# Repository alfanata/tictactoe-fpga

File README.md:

# Tic Tac Toe game for ice40 FPGA (HX8K)

* Simple tic-tac-toe game for the HX8K FPGA breakout board.

* Can both be played against AI or with 2 human players by setting a switch.

* The AI is based on generating the gametree using the python script and then storing all moves in the BRAM of the FPGA as a ROM. The python script generates the entire BRAM block initialization code.

* A PCB design is also provided that can plug directly into the HX8K breakout board. 

* To support other FPGA's you will have to modify the tictactoe_ram entity to fit other native BRAM types.

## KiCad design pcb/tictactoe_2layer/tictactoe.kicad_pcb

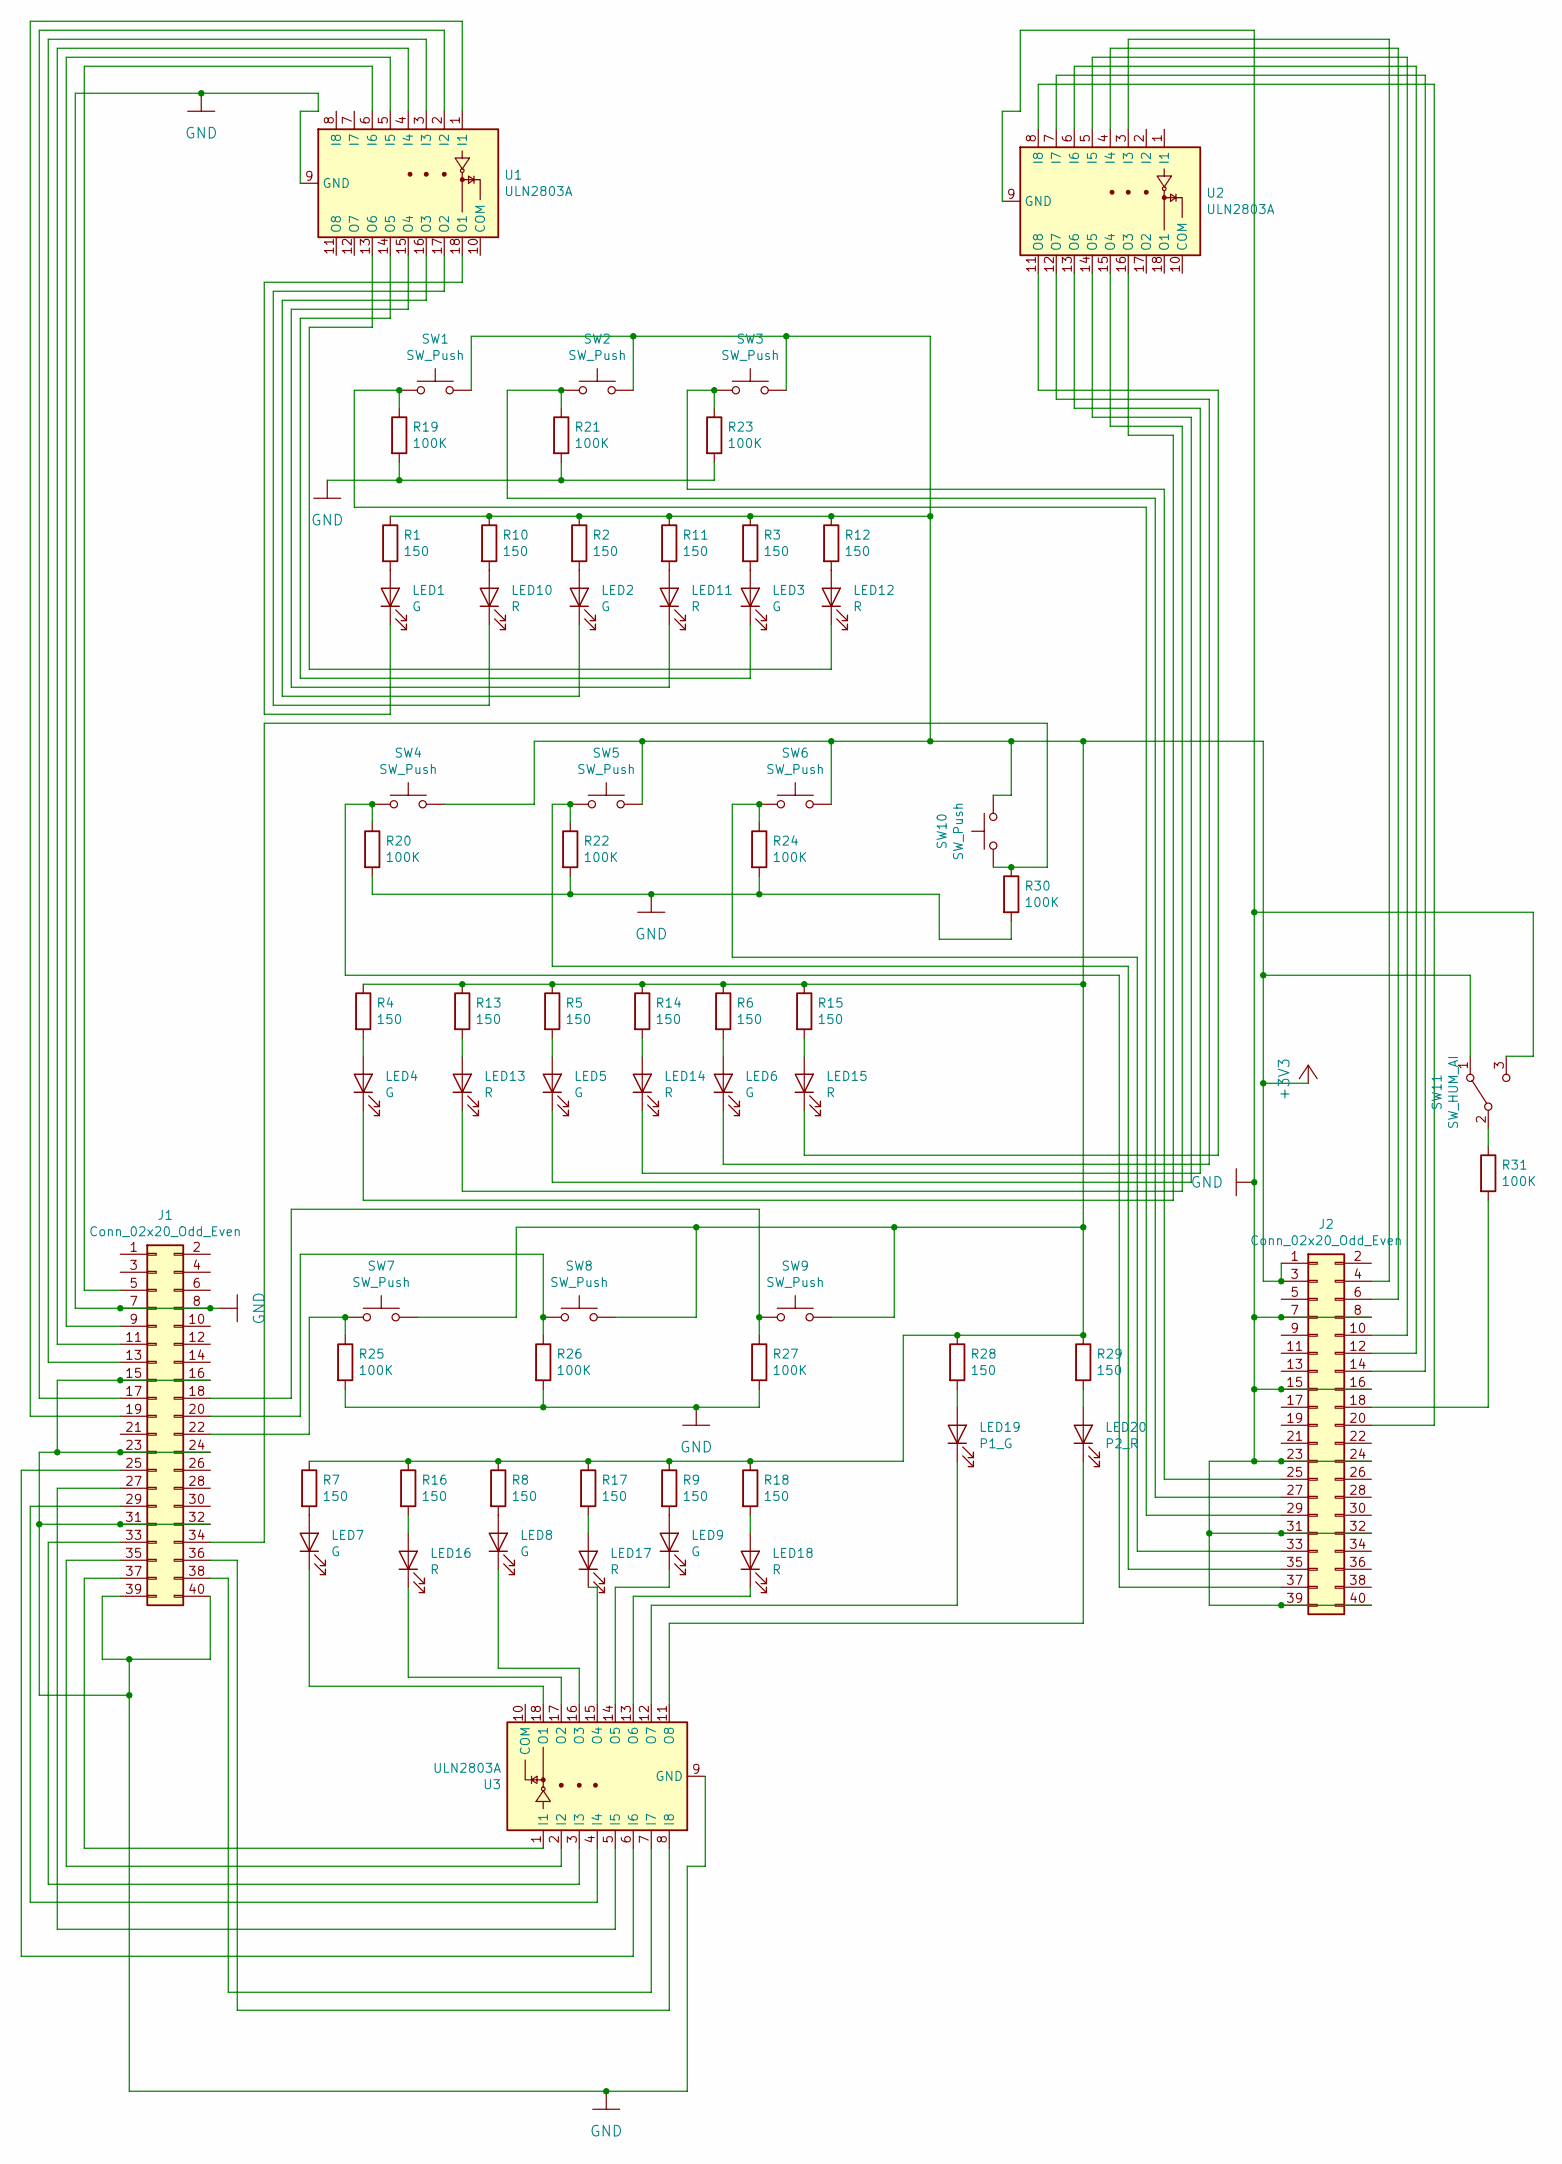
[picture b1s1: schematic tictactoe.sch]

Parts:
J1, J2: Conn_02x20_Odd_Even; PinHeader_2x20_P2.54mm_Vertical
LED1, LED2, LED3, LED4, LED5, LED6, LED7, LED8, LED9: G; LED_D3.0mm
LED10, LED11, LED12, LED13, LED14, LED15, LED16, LED17, LED18: R; LED_D3.0mm
LED19: P1_G; LED_D3.0mm
LED20: P2_R; LED_D3.0mm
R1, R2, R3, R4, R5, R6, R7, R8, R9, R10, R11, R12, R13, R14, R15, R16, R17, R18, R28, R29: 150; R_Axial_DIN0207_L6.3mm_D2.5mm_P10.16mm_Horizontal
R19, R20, R21, R22, R23, R24, R25, R26, R27, R30, R31: 100K; R_Axial_DIN0207_L6.3mm_D2.5mm_P10.16mm_Horizontal
SW1, SW2, SW3, SW4, SW5, SW6, SW7, SW8, SW9, SW10: SW_Push; SW_PUSH_6mm
SW11: SW_HUM_AI; SS12D00
U1, U2, U3: ULN2803A; DIP-18_W7.62mm_Socket

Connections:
+3V3: J2.1, J2.3, R1.1, R2.1, R3.1, R4.1, R5.1, R6.1, R7.1, R8.1, R9.1, R10.1, R11.1, R12.1, R13.1, R14.1, R15.1, R16.1, R17.1, R18.1, R28.1, R29.1, SW1.2, SW2.2, SW3.2, SW4.2, SW5.2, SW6.2, SW7.2, SW8.2, SW9.2, SW10.2, SW11.1 (A)
GND: J1.7, J1.8, J1.15, J1.16, J1.23, J1.24, J1.31, J1.32, J1.39, J1.40, J2.7, J2.8, J2.15, J2.16, J2.23, J2.24, J2.31, J2.32, J2.39, J2.40, R19.2, R20.2, R21.2, R22.2, R23.2, R24.2, R25.2, R26.2, R27.2, R30.2, SW11.3 (C), U1.9 (GND), U2.9 (GND), U3.9 (GND)
unnamed: J1.5, U1.6 (I6)
unnamed: J1.9, U1.5 (I5)
unnamed: J1.11, U1.4 (I4)
unnamed: J1.13, U1.3 (I3)
unnamed: J1.17, U1.2 (I2)
unnamed: J1.18, R27.1, SW9.1
unnamed: J1.19, U1.1 (I1)
unnamed: J1.20, R26.1, SW8.1
unnamed: J1.22, R25.1, SW7.1
unnamed: J1.25, U3.6 (I6)
unnamed: J1.27, U3.5 (I5)
unnamed: J1.29, U3.4 (I4)
unnamed: J1.33, U3.3 (I3)
unnamed: J1.34, R30.1, SW10.1
unnamed: J1.35, U3.2 (I2)
unnamed: J1.36, U3.8 (I8)
unnamed: J1.37, U3.1 (I1)
unnamed: J1.38, U3.7 (I7)
unnamed: J2.4, U2.3 (I3)
unnamed: J2.6, U2.4 (I4)
unnamed: J2.10, U2.5 (I5)
unnamed: J2.12, U2.6 (I6)
unnamed: J2.14, U2.7 (I7)
unnamed: J2.18, R31.2
unnamed: J2.20, U2.8 (I8)
unnamed: J2.25, R23.1, SW3.1
unnamed: J2.27, R21.1, SW2.1
unnamed: J2.29, R19.1, SW1.1
unnamed: J2.33, R24.1, SW6.1
unnamed: J2.35, R22.1, SW5.1
unnamed: J2.37, R20.1, SW4.1
unnamed: LED1.1 (K), U1.18 (O1)
unnamed: LED1.2 (A), R1.2
unnamed: LED2.1 (K), U1.16 (O3)
unnamed: LED2.2 (A), R2.2
unnamed: LED3.1 (K), U1.14 (O5)
unnamed: LED3.2 (A), R3.2
unnamed: LED4.1 (K), U2.16 (O3)
unnamed: LED4.2 (A), R4.2
unnamed: LED5.1 (K), U2.14 (O5)
unnamed: LED5.2 (A), R5.2
unnamed: LED6.1 (K), U2.12 (O7)
unnamed: LED6.2 (A), R6.2
unnamed: LED7.1 (K), U3.18 (O1)
unnamed: LED7.2 (A), R7.2
unnamed: LED8.1 (K), U3.16 (O3)
unnamed: LED8.2 (A), R8.2
unnamed: LED9.1 (K), U3.14 (O5)
unnamed: LED9.2 (A), R9.2
unnamed: LED10.1 (K), U1.17 (O2)
unnamed: LED10.2 (A), R10.2
unnamed: LED11.1 (K), U1.15 (O4)
unnamed: LED11.2 (A), R11.2
unnamed: LED12.1 (K), U1.13 (O6)
unnamed: LED12.2 (A), R12.2
unnamed: LED13.1 (K), U2.15 (O4)
unnamed: LED13.2 (A), R13.2
unnamed: LED14.1 (K), U2.13 (O6)
unnamed: LED14.2 (A), R14.2
unnamed: LED15.1 (K), U2.11 (O8)
unnamed: LED15.2 (A), R15.2
unnamed: LED16.1 (K), U3.17 (O2)
unnamed: LED16.2 (A), R16.2
unnamed: LED17.1 (K), U3.15 (O4)
unnamed: LED17.2 (A), R17.2
unnamed: LED18.1 (K), U3.13 (O6)
unnamed: LED18.2 (A), R18.2
unnamed: LED19.1 (K), U3.12 (O7)
unnamed: LED19.2 (A), R28.2
unnamed: LED20.1 (K), U3.11 (O8)
unnamed: LED20.2 (A), R29.2
unnamed: R31.1, SW11.2 (B)

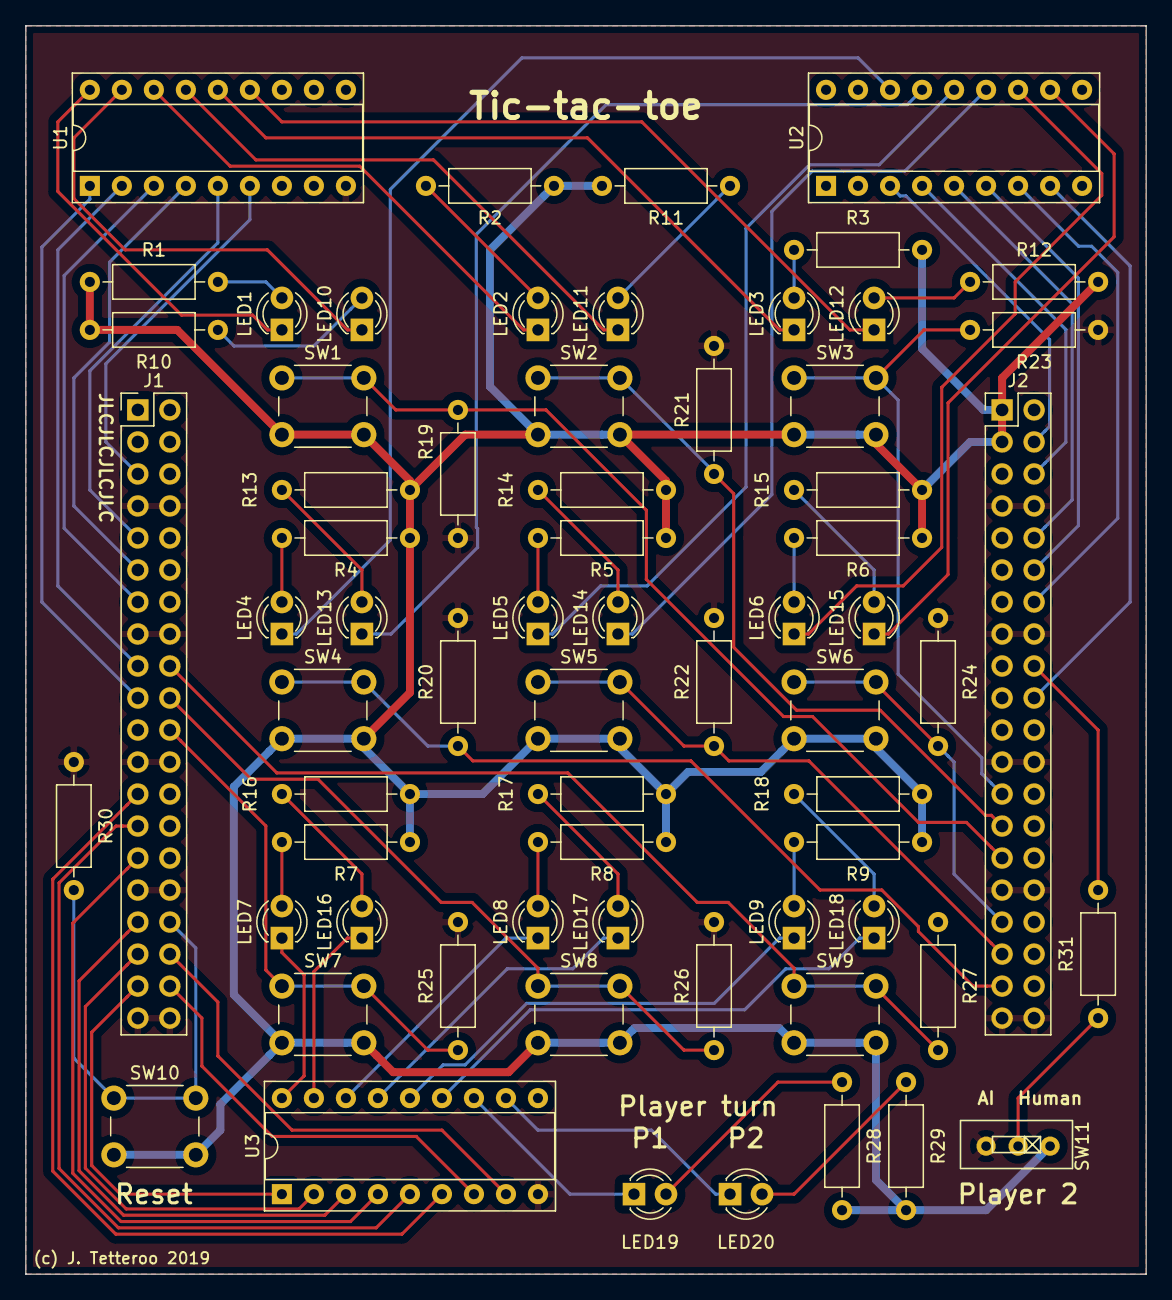
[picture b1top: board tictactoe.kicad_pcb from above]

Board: 2 copper layers, 88.9 x 99.1 mm, 67 parts (0 on the bottom side), 74 nets.

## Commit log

2019-10-27 all code and stuff
2019-10-27 readme fixed
